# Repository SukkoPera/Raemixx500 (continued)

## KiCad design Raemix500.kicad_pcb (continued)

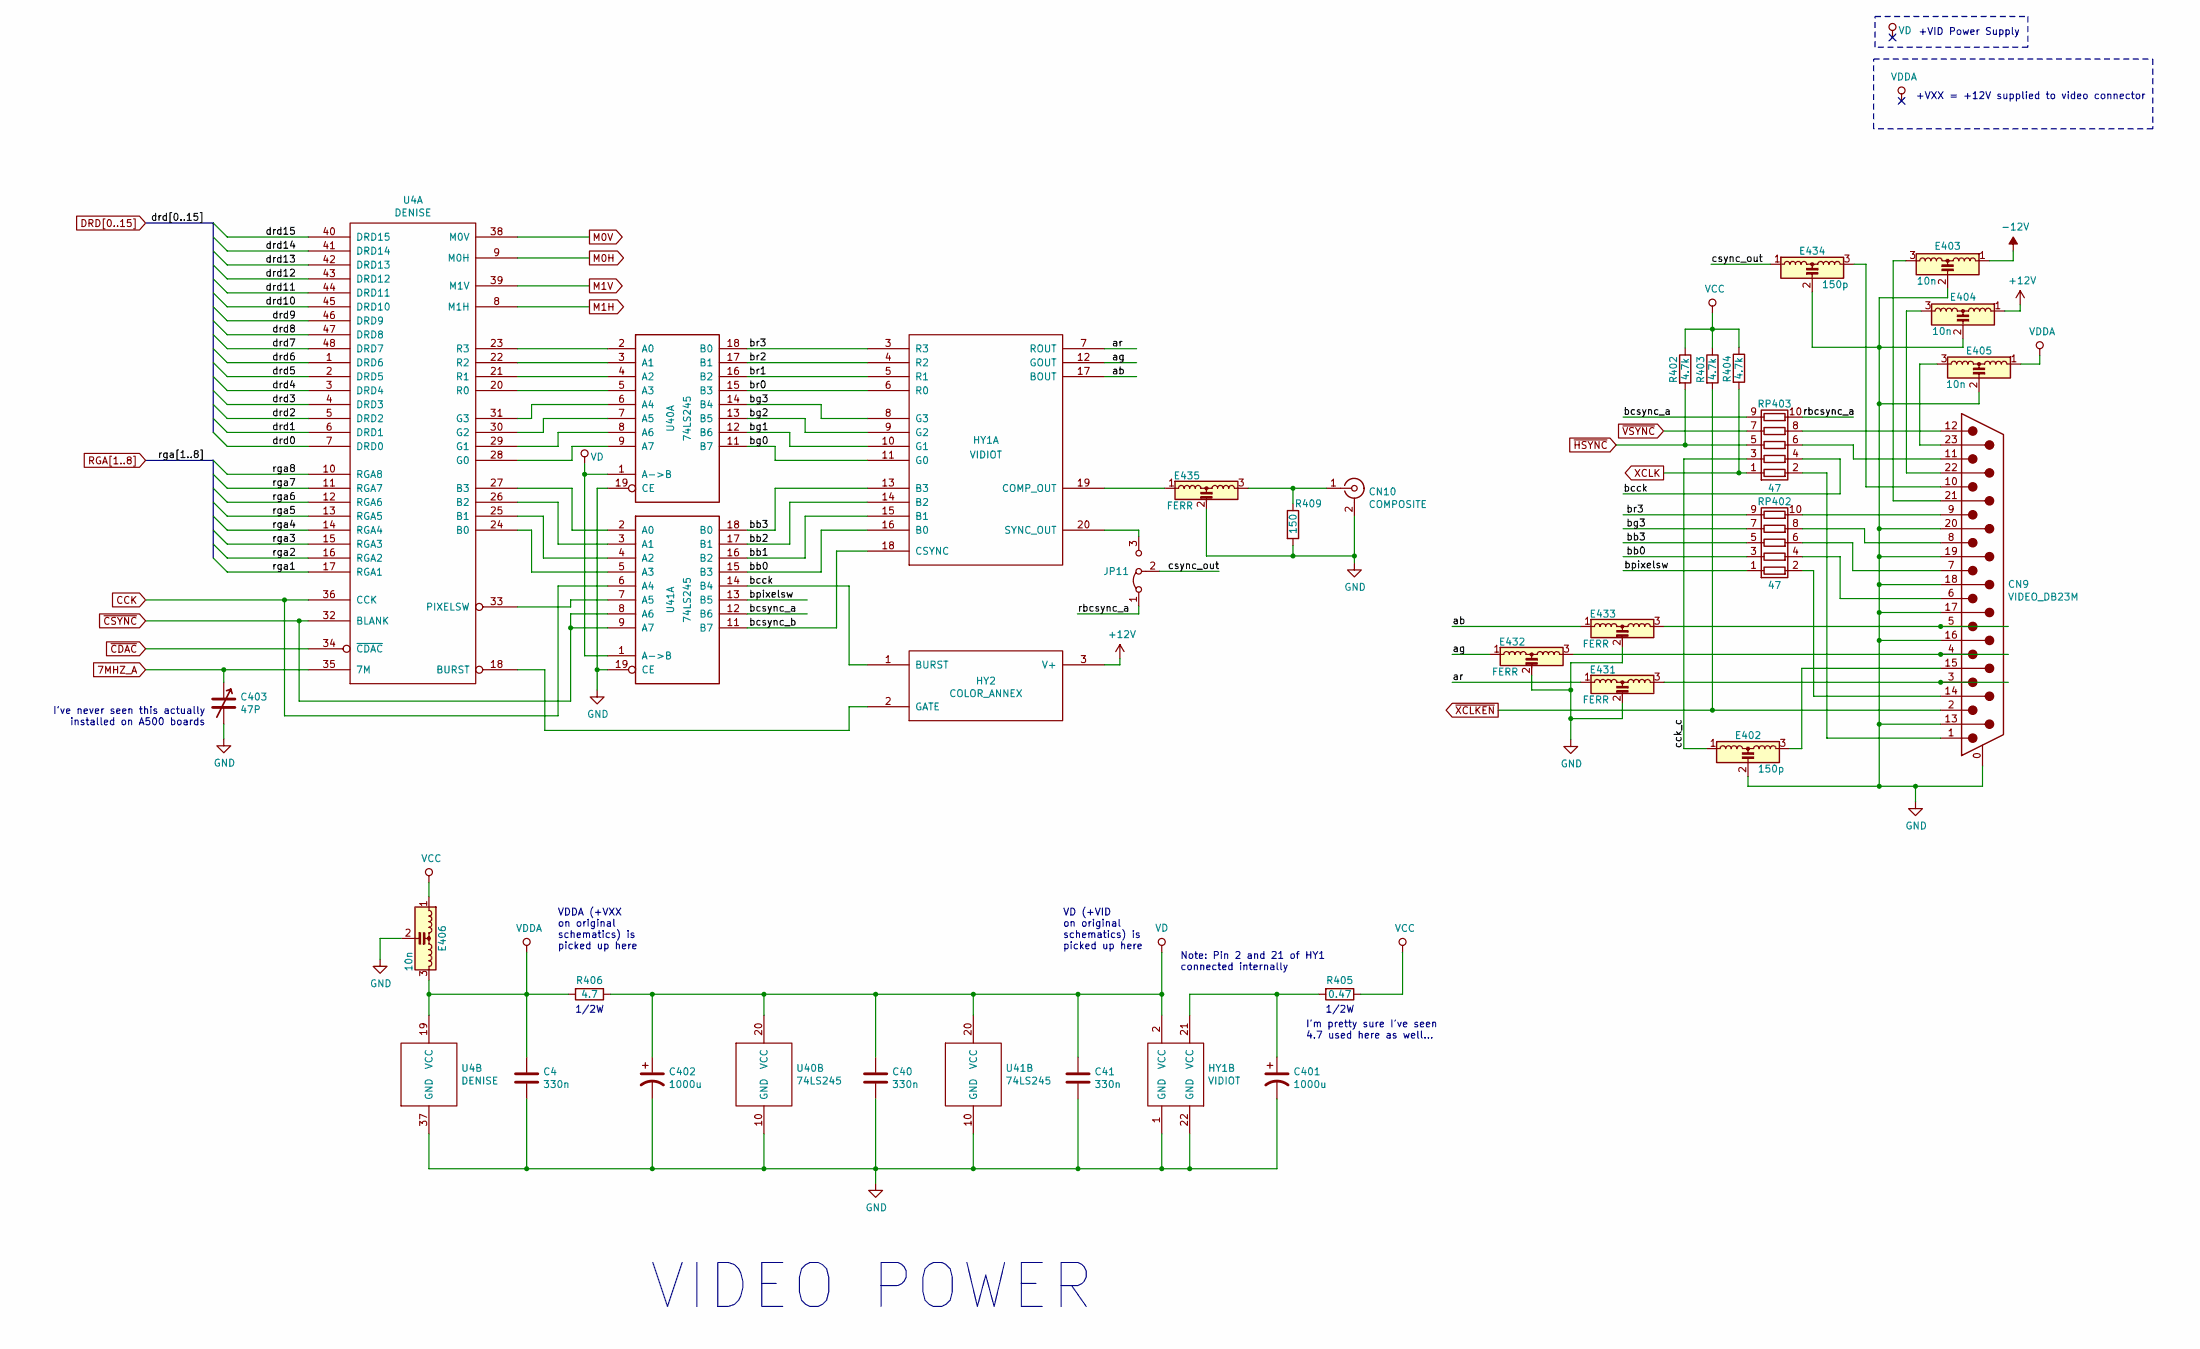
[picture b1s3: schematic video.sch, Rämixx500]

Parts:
C4, C40, C41: 330n; C_Axial_L6.3mm_D2.5mm_P10.16mm
C401, C402: 1000u; CP_Radial_D8.0mm_P5.00mm
C403: 47P; VariCap
CN9: VIDEO_DB23M; DB_23
CN10: COMPOSITE; rca_yellow
E402, E434: 150p; EMI_Filter_Long
E403, E404, E405: 10n; EMI_Filter_Long
E406: 10n; EMI_Filter_Short
E431, E432, E433, E435: FERR; EMI_Filter_Long
HY1: VIDIOT; PinHeader_1x22_P2.54mm_Vertical
HY2: COLOR_ANNEX; PinHeader_1x03_P2.54mm_Vertical
JP11: Jumper_3_Bridged12; Jumper3-Bridged12
R402, R403, R404: 4.7k; R_Axial_DIN0309_L9.0mm_D3.2mm_P12.70mm_Horizontal
R405: 0.47; R_Axial_DIN0309_L9.0mm_D3.2mm_P15.24mm_Horizontal
R406: 4.7; R_Axial_DIN0309_L9.0mm_D3.2mm_P15.24mm_Horizontal
R409: 150; C_Axial_L9.0mm_D3.2mm_P12.70mm
RP402, RP403: 47; R_Array_SIP10
U4: DENISE; DIP-48_W15.24mm_Socket_LongPads
U40, U41: 74LS245; DIP-20_W7.62mm_Socket_LongPads

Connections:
7MHZ_A: C403.1, U4.35 (7M); also elsewhere on the board
+12V: E404.1, HY2.3 (V+); also elsewhere on the board
-12V: E403.1; also elsewhere on the board
/Denise & Video Stuff/ab: E433.1, HY1.17 (BOUT)
/Denise & Video Stuff/ag: E432.1, HY1.12 (GOUT)
/Denise & Video Stuff/ar: E431.1, HY1.7 (ROUT)
/Denise & Video Stuff/bb0: HY1.16 (B0), RP402.3 (R2.1), U41.15 (B3)
/Denise & Video Stuff/bb1: HY1.15 (B1), U41.16 (B2)
/Denise & Video Stuff/bb2: HY1.14 (B2), U41.17 (B1)
/Denise & Video Stuff/bb3: HY1.13 (B3), RP402.5 (R3.1), U41.18 (B0)
/Denise & Video Stuff/bcck: HY2.1 (BURST), RP403.4 (R2.2), U41.14 (B4)
/Denise & Video Stuff/bcsync_a: RP403.9 (R5.1), U41.12 (B6)
/Denise & Video Stuff/bcsync_b: HY1.18 (CSYNC), U41.11 (B7)
/Denise & Video Stuff/bg0: HY1.11 (G0), U40.11 (B7)
/Denise & Video Stuff/bg1: HY1.10 (G1), U40.12 (B6)
/Denise & Video Stuff/bg2: HY1.9 (G2), U40.13 (B5)
/Denise & Video Stuff/bg3: HY1.8 (G3), RP402.7 (R4.1), U40.14 (B4)
/Denise & Video Stuff/bpixelsw: RP402.1 (R1.1), U41.13 (B5)
/Denise & Video Stuff/br0: HY1.6 (R0), U40.15 (B3)
/Denise & Video Stuff/br1: HY1.5 (R1), U40.16 (B2)
/Denise & Video Stuff/br2: HY1.4 (R2), U40.17 (B1)
/Denise & Video Stuff/br3: HY1.3 (R3), RP402.9 (R5.1), U40.18 (B0)
/Denise & Video Stuff/cck_c: E402.1, RP403.3 (R2.1)
/Denise & Video Stuff/csync_out: E434.1, JP11.2 (C)
/Denise & Video Stuff/rbcsync_a: JP11.1 (A), RP403.10 (R5.2)
CCK: U4.36 (CCK), U41.6 (A4); also elsewhere on the board
DRD0: U4.7 (DRD0); also elsewhere on the board
DRD1: U4.6 (DRD1); also elsewhere on the board
DRD2: U4.5 (DRD2); also elsewhere on the board
DRD3: U4.4 (DRD3); also elsewhere on the board
DRD4: U4.3 (DRD4); also elsewhere on the board
DRD5: U4.2 (DRD5); also elsewhere on the board
DRD6: U4.1 (DRD6); also elsewhere on the board
DRD7: U4.48 (DRD7); also elsewhere on the board
DRD8: U4.47 (DRD8); also elsewhere on the board
DRD9: U4.46 (DRD9); also elsewhere on the board
DRD10: U4.45 (DRD10); also elsewhere on the board
DRD11: U4.44 (DRD11); also elsewhere on the board
DRD12: U4.43 (DRD12); also elsewhere on the board
DRD13: U4.42 (DRD13); also elsewhere on the board
DRD14: U4.41 (DRD14); also elsewhere on the board
DRD15: U4.40 (DRD15); also elsewhere on the board
GND: C4.2, C40.2, C41.2, C401.2, C402.2, C403.2, CN9.0 (PAD), CN9.13, CN9.16, CN9.17, CN9.18, CN9.19, CN9.20, CN10.2 (Ext), E402.2, E403.2, E404.2, E405.2, E406.2, E431.2, E432.2, E433.2, E434.2, E435.2, HY1.1 (GND), HY1.22 (GND), R409.2, U4.37 (GND), U40.10 (GND), U40.19 (CE), U41.10 (GND), U41.19 (CE); also elsewhere on the board
M0H: U4.9 (M0H); also elsewhere on the board
M0V: U4.38 (M0V); also elsewhere on the board
M1H: U4.8 (M1H); also elsewhere on the board
M1V: U4.39 (M1V); also elsewhere on the board
unnamed: C401.1, HY1.21 (VCC), R405.2
unnamed: CN9.1, RP403.2 (R1.2)
unnamed: CN9.3, E431.3
unnamed: CN9.4, E432.3
unnamed: CN9.5, E433.3
unnamed: CN9.6, RP402.4 (R2.2)
unnamed: CN9.7, RP402.6 (R3.2)
unnamed: CN9.8, RP402.8 (R4.2)
unnamed: CN9.9, RP402.10 (R5.2)
unnamed: CN9.10, E434.3
unnamed: CN9.11, RP403.6 (R3.2)
unnamed: CN9.12, RP403.8 (R4.2)
unnamed: CN9.14, RP402.2 (R1.2)
unnamed: CN9.15, E402.3
unnamed: CN9.21, E403.3
unnamed: CN9.22, E404.3
unnamed: CN9.23, E405.3
unnamed: CN10.1 (In), E435.3, R409.1
unnamed: E435.1, HY1.19 (COMP_OUT)
unnamed: HY1.20 (SYNC_OUT), JP11.3 (B)
unnamed: HY2.2 (GATE), U4.18 (BURST)
unnamed: U4.20 (R0), U40.5 (A3)
unnamed: U4.21 (R1), U40.4 (A2)
unnamed: U4.22 (R2), U40.3 (A1)
unnamed: U4.23 (R3), U40.2 (A0)
unnamed: U4.24 (B0), U41.5 (A3)
unnamed: U4.25 (B1), U41.4 (A2)
unnamed: U4.26 (B2), U41.3 (A1)
unnamed: U4.27 (B3), U41.2 (A0)
unnamed: U4.28 (G0), U40.9 (A7)
unnamed: U4.29 (G1), U40.8 (A6)
unnamed: U4.30 (G2), U40.7 (A5)
unnamed: U4.31 (G3), U40.6 (A4)
unnamed: U4.33 (PIXELSW), U41.7 (A5)
RGA1: U4.17 (RGA1); also elsewhere on the board
RGA2: U4.16 (RGA2); also elsewhere on the board
RGA3: U4.15 (RGA3); also elsewhere on the board
RGA4: U4.14 (RGA4); also elsewhere on the board
RGA5: U4.13 (RGA5); also elsewhere on the board
RGA6: U4.12 (RGA6); also elsewhere on the board
RGA7: U4.11 (RGA7); also elsewhere on the board
RGA8: U4.10 (RGA8); also elsewhere on the board
VCC: E406.1, R402.1, R403.1, R404.1, R405.1; also elsewhere on the board
VD: C40.1, C41.1, C402.1, HY1.2 (VCC), R406.1, U40.1 (A->B), U40.20 (VCC), U41.1 (A->B), U41.20 (VCC)
VDDA: C4.1, E405.1, E406.3, R406.2, U4.19 (VCC)
XCLK: R404.2, RP403.1 (R1.1); also elsewhere on the board
~CDAC: U4.34 (~CDAC); also elsewhere on the board
~CSYNC: U4.32 (BLANK), U41.8 (A6), U41.9 (A7); also elsewhere on the board
~HSYNC: R402.2, RP403.5 (R3.1); also elsewhere on the board
~VSYNC: RP403.7 (R4.1); also elsewhere on the board

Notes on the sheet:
I've never seen this actually installed on A500 boards
+VID Power Supply
+VXX = +12V supplied to video connector
VDDA (+VXX on original schematics) is picked up here
1/2W
VD (+VID on original schematics) is picked up here
I'm pretty sure I've seen 4.7 used here as well...
Note: Pin 2 and 21 of HY1 connected internally
VIDEO POWER

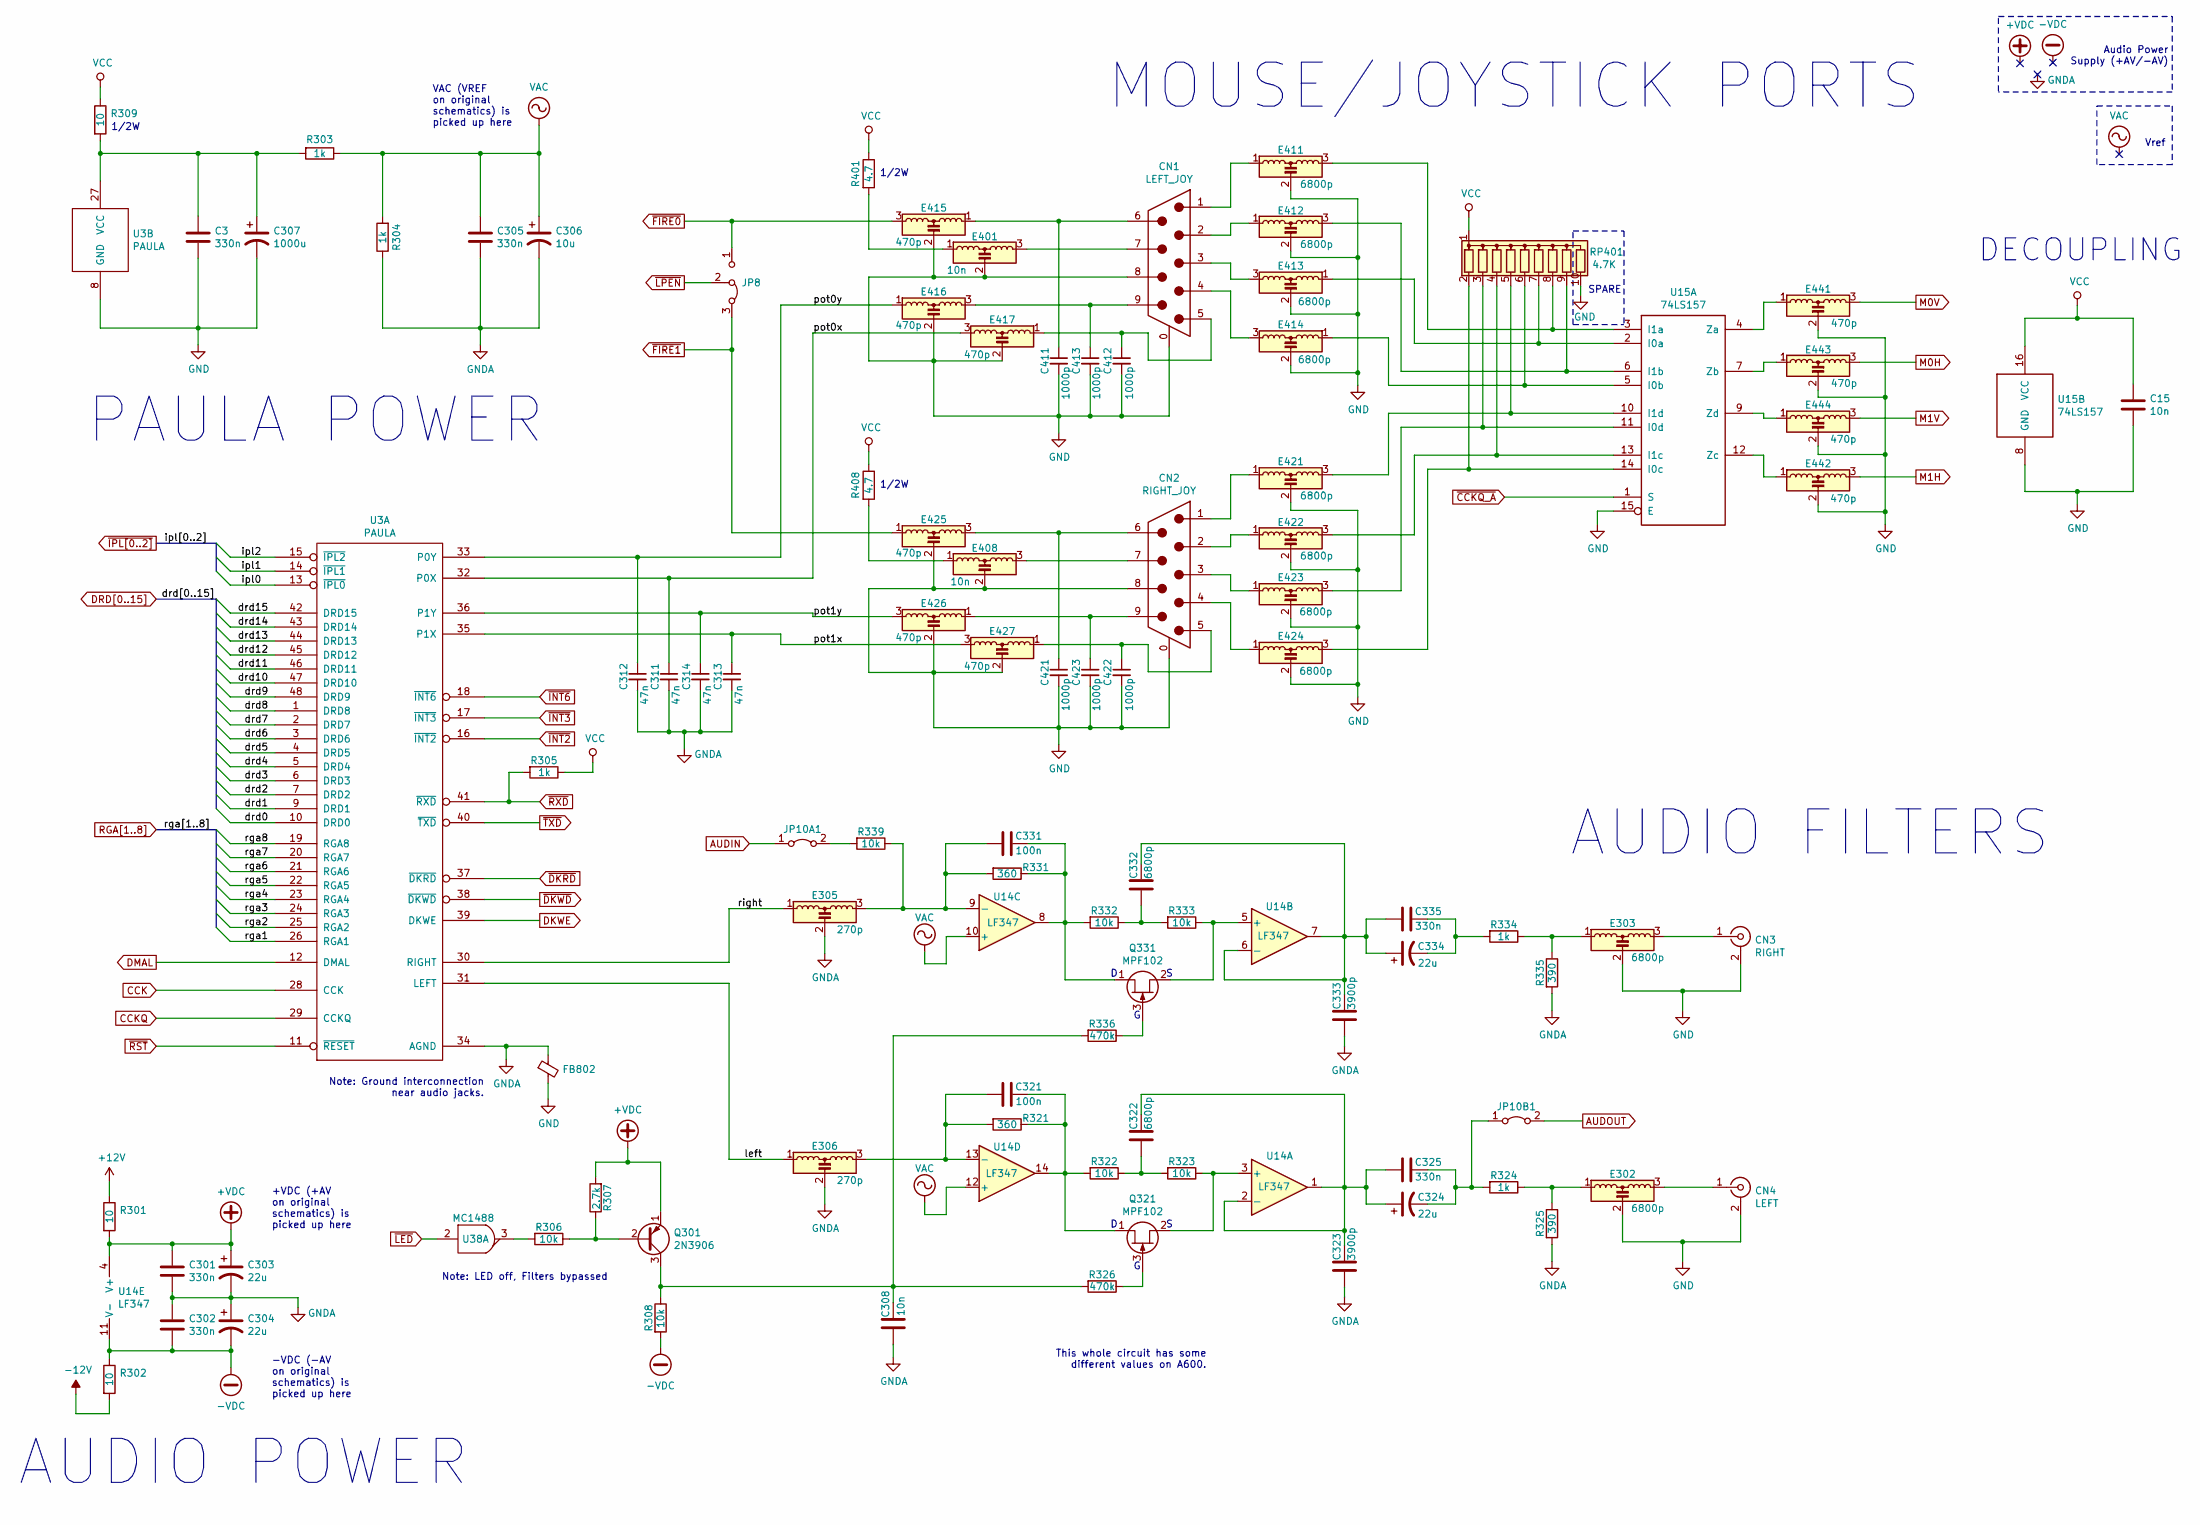
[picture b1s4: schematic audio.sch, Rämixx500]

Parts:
C3: 330n; C_Axial_L6.3mm_D2.5mm_P10.16mm
C15: 10n; C_Axial_L6.3mm_D2.5mm_P10.16mm
C301, C302, C305, C325, C335: 330n; C_Axial_L9.0mm_D3.2mm_P12.70mm
C303, C304: 22u; CP_Radial_D5.0mm_P2.00mm
C306: 10u; CP_Radial_D8.0mm_P5.00mm
C307: 1000u; CP_Radial_D8.0mm_P5.00mm
C308: 10n; C_Axial_L9.0mm_D3.2mm_P12.70mm
C311, C312, C313, C314: 47n; C_Axial_L9.0mm_D3.2mm_P12.70mm
C321, C331: 100n; C_Axial_L9.0mm_D3.2mm_P12.70mm
C322, C332: 6800p; C_Axial_L9.0mm_D3.2mm_P12.70mm
C323, C333: 3900p; C_Axial_L9.0mm_D3.2mm_P12.70mm
C324, C334: 22u; CP_Radial_D8.0mm_P5.00mm
C411, C412, C413, C421, C422, C423: 1000p; C_Axial_L9.0mm_D3.2mm_P12.70mm
CN1: LEFT_JOY; DB_9M
CN2: RIGHT_JOY; DB_9M
CN3: RIGHT; rca_red
CN4: LEFT; rca_white
E302, E303: 6800p; EMI_Filter_Short
E305, E306: 270p; EMI_Filter_Long
E401, E408: 10n; EMI_Filter_Long
E411, E412, E413, E414, E421, E422, E423, E424: 6800p; EMI_Filter_Long
E415, E416, E417, E425, E426, E427, E441, E442, E443, E444: 470p; EMI_Filter_Long
FB802: Ferrite_Bead_Small; Ferrite_Axial_L9.0mm_D3.2mm_P12.70mm
JP8: Jumper_3_Bridged23; Jumper3-Bridged23
JP10A1, JP10B1: Jumper_2_Bridged; Jumper2-Bridged
Q301: 2N3906; TO-92L_Inline_Wide
Q321, Q331: MPF102; TO-92L_Inline_Wide
R301, R302: 10; R_Axial_DIN0309_L9.0mm_D3.2mm_P12.70mm_Horizontal
R303, R304, R305, R324, R334: 1k; R_Axial_DIN0309_L9.0mm_D3.2mm_P12.70mm_Horizontal
R306, R308, R322, R323, R332, R333, R339: 10k; R_Axial_DIN0309_L9.0mm_D3.2mm_P12.70mm_Horizontal
R307: 2.7k; R_Axial_DIN0309_L9.0mm_D3.2mm_P12.70mm_Horizontal
R309: 10; R_Axial_DIN0309_L9.0mm_D3.2mm_P15.24mm_Horizontal
R321, R331: 360; R_Axial_DIN0309_L9.0mm_D3.2mm_P12.70mm_Horizontal
R325, R335: 390; R_Axial_DIN0309_L9.0mm_D3.2mm_P12.70mm_Horizontal
R326, R336: 470k; R_Axial_DIN0309_L9.0mm_D3.2mm_P12.70mm_Horizontal
R401, R408: 4.7; R_Axial_DIN0309_L9.0mm_D3.2mm_P15.24mm_Horizontal
RP401: 4.7K; R_Array_SIP10
U3: PAULA; DIP-48_W15.24mm_Socket_LongPads
U14: LF347; DIP-14_W7.62mm_Socket_LongPads
U15: 74LS157; DIP-16_W7.62mm_Socket_LongPads
U38: MC1488; DIP-14_W7.62mm_Socket_LongPads

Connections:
+12V: R301.1; also elsewhere on the board
+VDC: C301.1, C303.1, Q301.1 (E), R301.2, R307.2, U14.4 (V+)
-12V: R302.2; also elsewhere on the board
-VDC: C302.2, C304.2, R302.1, R308.2, U14.11 (V-)
/Paula & Audio Stuff/left: E306.1, U3.31 (LEFT)
/Paula & Audio Stuff/pot0x: C311.1, E417.3, U3.32 (P0X)
/Paula & Audio Stuff/pot0y: C312.1, E416.1, U3.33 (P0Y)
/Paula & Audio Stuff/pot1x: C313.1, E427.3, U3.35 (P1X)
/Paula & Audio Stuff/pot1y: C314.1, E426.3, U3.36 (P1Y)
/Paula & Audio Stuff/right: E305.1, U3.30 (RIGHT)
AUDIN: JP10A1.1 (A); also elsewhere on the board
AUDOUT: JP10B1.2 (B); also elsewhere on the board
CCK: U3.28 (CCK); also elsewhere on the board
CCKQ: U3.29 (CCKQ); also elsewhere on the board
DKWE: U3.39 (DKWE); also elsewhere on the board
DMAL: U3.12 (DMAL); also elsewhere on the board
DRD0: U3.10 (DRD0); also elsewhere on the board
DRD1: U3.9 (DRD1); also elsewhere on the board
DRD2: U3.7 (DRD2); also elsewhere on the board
DRD3: U3.6 (DRD3); also elsewhere on the board
DRD4: U3.5 (DRD4); also elsewhere on the board
DRD5: U3.4 (DRD5); also elsewhere on the board
DRD6: U3.3 (DRD6); also elsewhere on the board
DRD7: U3.2 (DRD7); also elsewhere on the board
DRD8: U3.1 (DRD8); also elsewhere on the board
DRD9: U3.48 (DRD9); also elsewhere on the board
DRD10: U3.47 (DRD10); also elsewhere on the board
DRD11: U3.46 (DRD11); also elsewhere on the board
DRD12: U3.45 (DRD12); also elsewhere on the board
DRD13: U3.44 (DRD13); also elsewhere on the board
DRD14: U3.43 (DRD14); also elsewhere on the board
DRD15: U3.42 (DRD15); also elsewhere on the board
GND: C3.2, C15.2, C307.2, C411.2, C412.2, C413.2, C421.2, C422.2, C423.2, CN1.0 (PAD), CN1.8, CN2.0 (PAD), CN2.8, CN3.2 (Ext), CN4.2 (Ext), E302.2, E303.2, E401.2, E408.2, E411.2, E412.2, E413.2, E414.2, E415.2, E416.2, E417.2, E421.2, E422.2, E423.2, E424.2, E425.2, E426.2, E427.2, E441.2, E442.2, E443.2, E444.2, FB802.2, RP401.10 (R9), U3.8 (GND), U15.8 (GND), U15.15 (E); also elsewhere on the board
GNDA: C301.2, C302.1, C303.2, C304.1, C305.2, C306.2, C308.2, C311.2, C312.2, C313.2, C314.2, C323.2, C333.2, E305.2, E306.2, FB802.1, R304.1, R325.2, R335.2, U3.34 (AGND)
M0H: E443.3; also elsewhere on the board
M0V: E441.3; also elsewhere on the board
M1H: E442.3; also elsewhere on the board
M1V: E444.3; also elsewhere on the board
unnamed: C3.1, C307.1, R303.2, R309.2, U3.27 (VCC)
unnamed: C308.1, Q301.3 (C), R308.1, R326.2, R336.2
unnamed: C321.1, Q321.1 (D), R321.1, R322.2, U14.14
unnamed: C321.2, E306.3, R321.2, U14.13 (-)
unnamed: C322.1, C323.1, C324.1, C325.2, U14.1, U14.2 (-)
unnamed: C322.2, R322.1, R323.2
unnamed: C324.2, C325.1, JP10B1.1 (A), R324.2
unnamed: C331.1, Q331.1 (D), R331.1, R332.2, U14.8
unnamed: C331.2, E305.3, R331.2, R339.1, U14.9 (-)
unnamed: C332.1, C333.1, C334.1, C335.2, U14.6 (-), U14.7
unnamed: C332.2, R332.1, R333.2
unnamed: C334.2, C335.1, R334.2
unnamed: C411.1, CN1.6, E415.1
unnamed: C412.1, CN1.5, E417.1
unnamed: C413.1, CN1.9, E416.3
unnamed: C421.1, CN2.6, E425.3
unnamed: C422.1, CN2.5, E427.1
unnamed: C423.1, CN2.9, E426.1
unnamed: CN1.1, E411.1
unnamed: CN1.2, E412.1
unnamed: CN1.3, E413.3
unnamed: CN1.4, E414.3
unnamed: CN1.7, E401.3
unnamed: CN2.1, E421.1
unnamed: CN2.2, E422.1
unnamed: CN2.3, E423.1
unnamed: CN2.4, E424.1
unnamed: CN2.7, E408.3
unnamed: CN3.1 (In), E303.3
unnamed: CN4.1 (In), E302.3
unnamed: E302.1, R324.1, R325.1
unnamed: E303.1, R334.1, R335.1
unnamed: E401.1, R401.2
unnamed: E408.1, R408.2
unnamed: E411.3, RP401.8 (R7), U15.3 (I1a)
unnamed: E412.3, RP401.9 (R8), U15.6 (I1b)
unnamed: E413.1, RP401.7 (R6), U15.2 (I0a)
unnamed: E414.1, RP401.6 (R5), U15.5 (I0b)
unnamed: E421.3, RP401.5 (R4), U15.10 (I1d)
unnamed: E422.3, RP401.4 (R3), U15.13 (I1c)
unnamed: E423.3, RP401.3 (R2), U15.11 (I0d)
unnamed: E424.3, RP401.2 (R1), U15.14 (I0c)
unnamed: E441.1, U15.4 (Za)
unnamed: E442.1, U15.12 (Zc)
unnamed: E443.1, U15.7 (Zb)
unnamed: E444.1, U15.9 (Zd)
unnamed: JP10A1.2 (B), R339.2
unnamed: Q301.2 (B), R306.1, R307.1
unnamed: Q321.2 (S), R323.1, U14.3 (+)
unnamed: Q321.3 (G), R326.1
unnamed: Q331.2 (S), R333.1, U14.5 (+)
unnamed: Q331.3 (G), R336.1
unnamed: R306.2, U38.3
RGA1: U3.26 (RGA1); also elsewhere on the board
RGA2: U3.25 (RGA2); also elsewhere on the board
RGA3: U3.24 (RGA3); also elsewhere on the board
RGA4: U3.23 (RGA4); also elsewhere on the board
RGA5: U3.22 (RGA5); also elsewhere on the board
RGA6: U3.21 (RGA6); also elsewhere on the board
RGA7: U3.20 (RGA7); also elsewhere on the board
RGA8: U3.19 (RGA8); also elsewhere on the board
VAC: C305.1, C306.1, R303.1, R304.2, U14.10 (+), U14.12 (+)
VCC: C15.1, R305.1, R309.1, R401.1, R408.1, RP401.1 (common), U15.16 (VCC); also elsewhere on the board
~CCKQ_A: U15.1 (S); also elsewhere on the board
~DKRD: U3.37 (~DKRD); also elsewhere on the board
~DKWD: U3.38 (~DKWD); also elsewhere on the board
~FIRE0: E415.3, JP8.1 (A); also elsewhere on the board
~FIRE1: E425.1, JP8.3 (B); also elsewhere on the board
~INT2: U3.16 (~INT2); also elsewhere on the board
~INT3: U3.17 (~INT3); also elsewhere on the board
~INT6: U3.18 (~INT6); also elsewhere on the board
~IPL0: U3.13 (~IPL0); also elsewhere on the board
~IPL1: U3.14 (~IPL1); also elsewhere on the board
~IPL2: U3.15 (~IPL2); also elsewhere on the board
~LED: U38.2; also elsewhere on the board
~LPEN: JP8.2 (C); also elsewhere on the board
~RST: U3.11 (~RESET); also elsewhere on the board
~RXD: R305.2, U3.41 (~RXD); also elsewhere on the board
~TXD: U3.40 (~TXD); also elsewhere on the board

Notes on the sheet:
Note: Ground interconnection near audio jacks.
Audio Power Supply (+AV/-AV)
1/2W
SPARE
Vref
Note: LED off, Filters bypassed
AUDIO FILTERS
MOUSE/JOYSTICK PORTS
This whole circuit has some different values on A600.
VAC (VREF on original schematics) is picked up here
+VDC (+AV on original schematics) is picked up here
-VDC (-AV on original schematics) is picked up here
PAULA POWER
AUDIO POWER
DECOUPLING

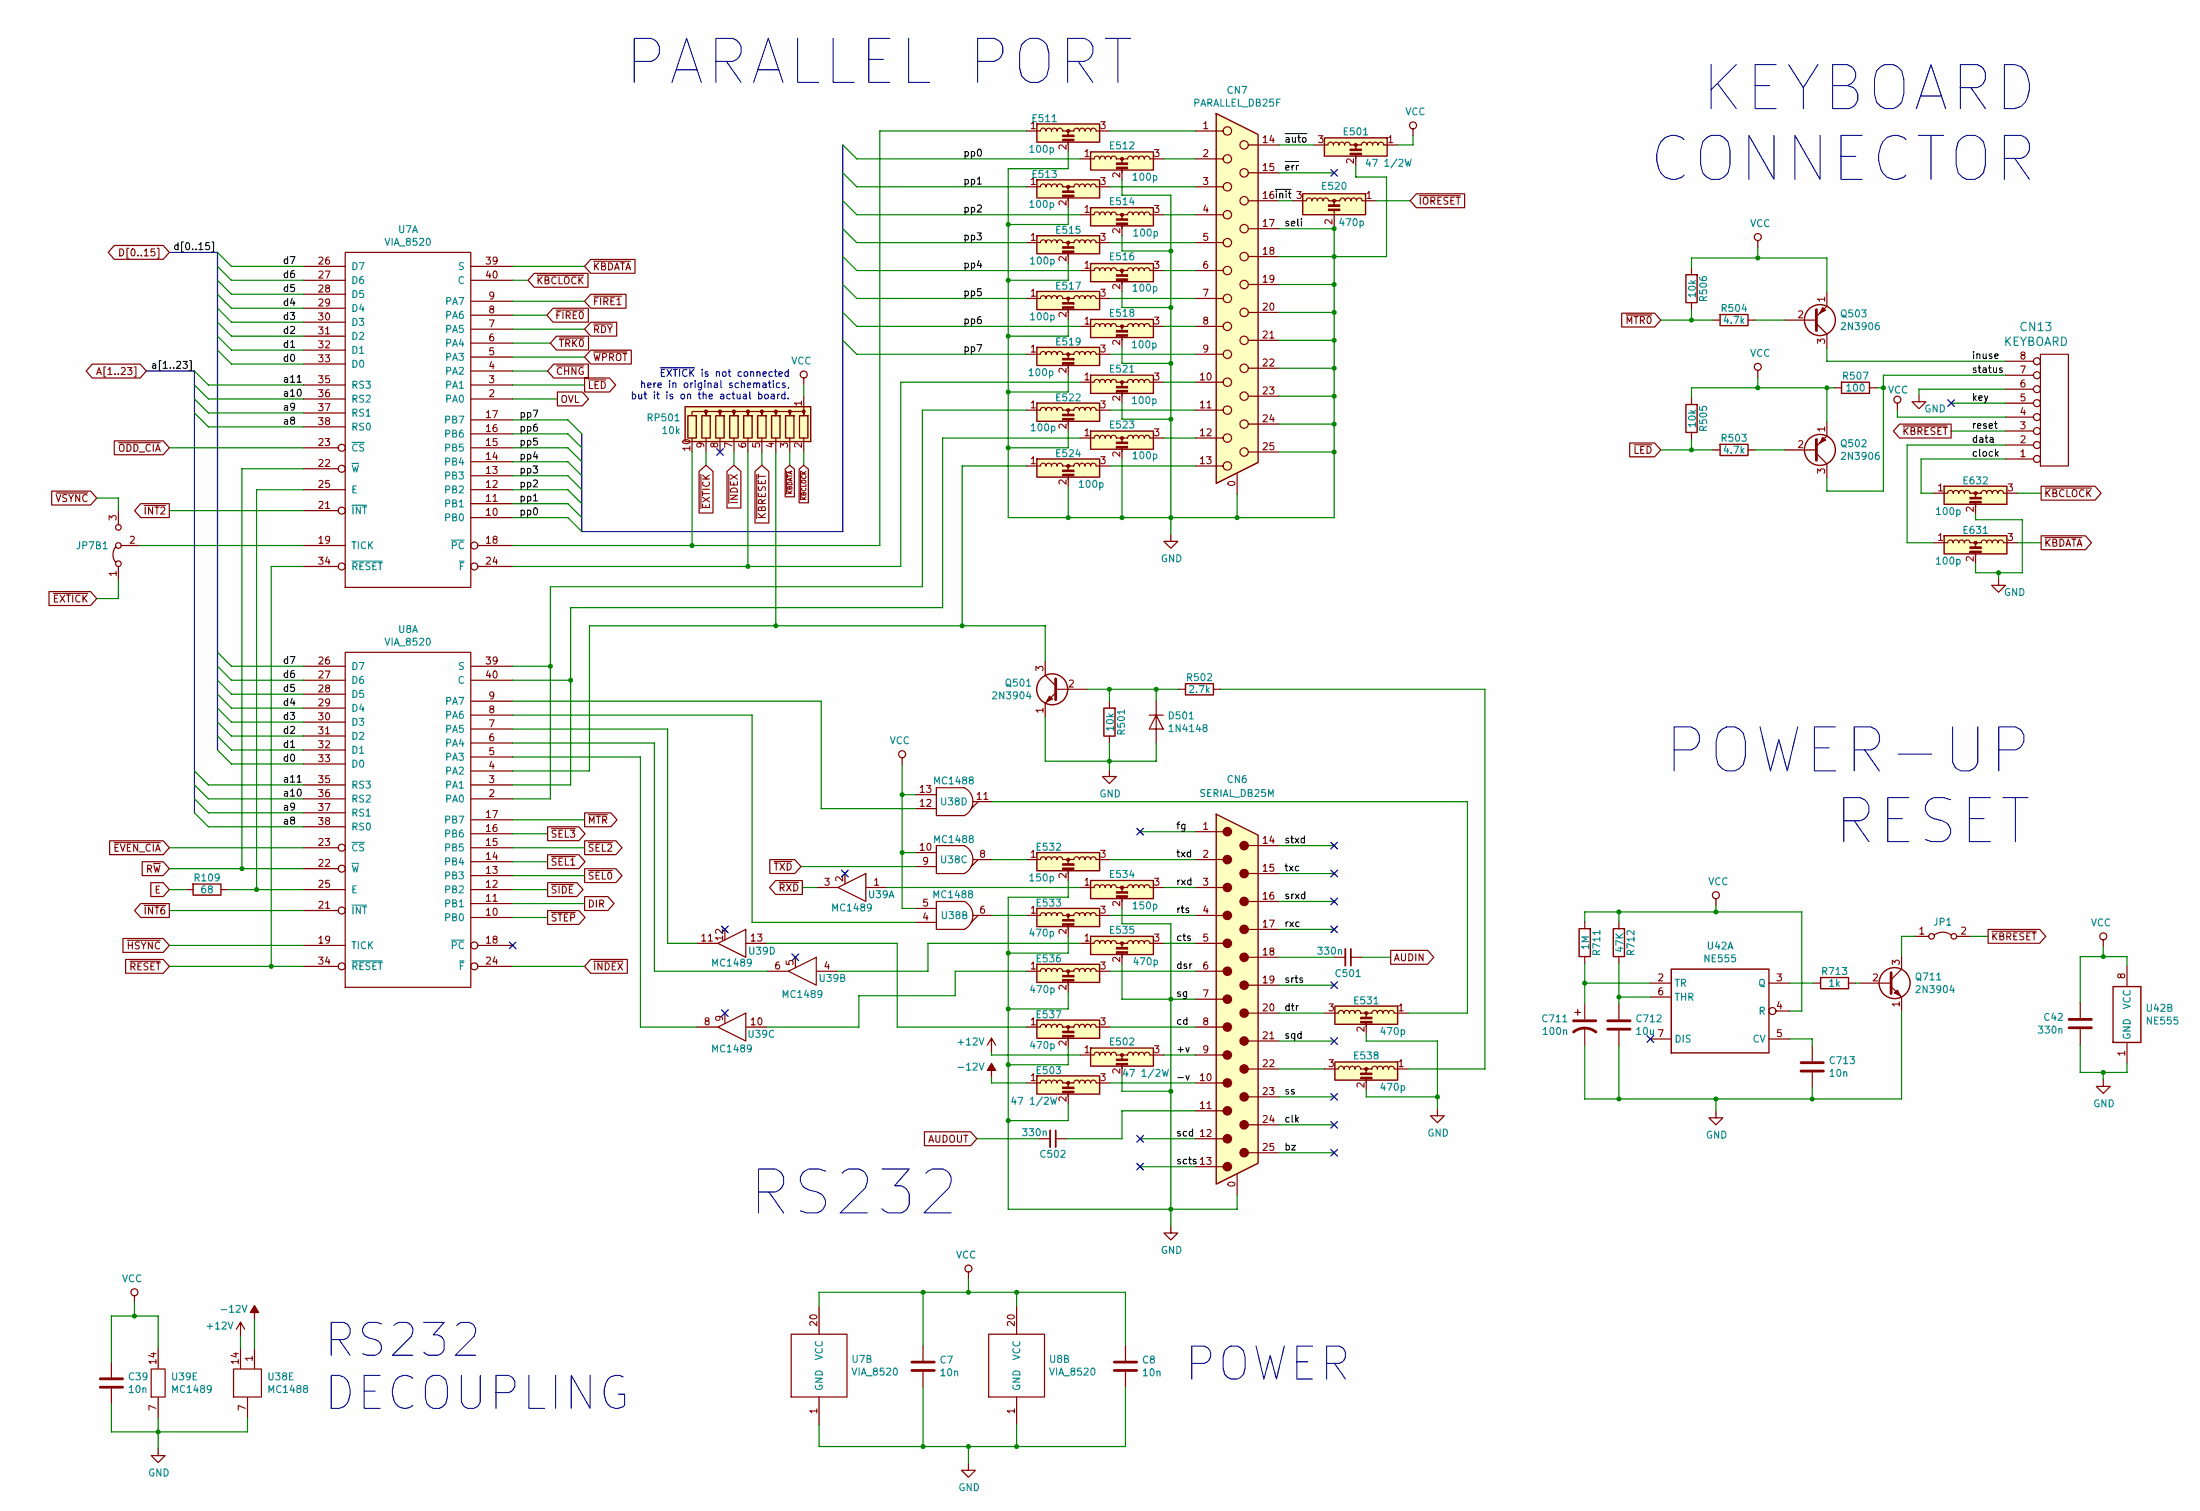
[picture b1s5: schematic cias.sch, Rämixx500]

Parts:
C7, C8: 10n; C_Axial_L6.3mm_D2.5mm_P10.16mm
C39, C713: 10n; C_Axial_L9.0mm_D3.2mm_P12.70mm
C42: 330n; C_Axial_L6.3mm_D2.5mm_P10.16mm
C501, C502: 330n; C_Axial_L9.0mm_D3.2mm_P12.70mm
C711: 100n; C_Axial_L9.0mm_D3.2mm_P12.70mm
C712: 10u; CP_Radial_D8.0mm_P5.00mm
CN6: SERIAL_DB25M; DB_25M
CN7: PARALLEL_DB25F; DB_25M
CN13: KEYBOARD; PinHeader_1x08_P2.54mm_Vertical
D501: 1N4148; D_DO-35_SOD27_P12.70mm_Horizontal
E501, E502, E503: 47 1/2W; EMI_Filter_Longer
E511, E512, E513, E514, E515, E516, E517, E518, E519, E521, E522, E523, E524, E631, E632: 100p; EMI_Filter_Short
E520, E531, E533, E535, E536, E537, E538: 470p; EMI_Filter_Short
E532, E534: 150p; EMI_Filter_Short
JP1: Jumper_2_Bridged; Jumper2-Bridged
JP7B1: Jumper_3_Bridged12; Jumper3-Bridged12
Q501, Q711: 2N3904; TO-92L_Inline_Wide
Q502, Q503: 2N3906; TO-92L_Inline_Wide
R109: 68; R_Axial_DIN0309_L9.0mm_D3.2mm_P12.70mm_Horizontal
R501, R505, R506: 10k; R_Axial_DIN0309_L9.0mm_D3.2mm_P12.70mm_Horizontal
R502: 2.7k; R_Axial_DIN0309_L9.0mm_D3.2mm_P12.70mm_Horizontal
R503, R504: 4.7k; R_Axial_DIN0309_L9.0mm_D3.2mm_P12.70mm_Horizontal
R507: 100; R_Axial_DIN0309_L9.0mm_D3.2mm_P12.70mm_Horizontal
R711: 1M; R_Axial_DIN0309_L9.0mm_D3.2mm_P12.70mm_Horizontal
R712: 47K; R_Axial_DIN0309_L9.0mm_D3.2mm_P12.70mm_Horizontal
R713: 1k; R_Axial_DIN0309_L9.0mm_D3.2mm_P12.70mm_Horizontal
RP501: 10k; R_Array_SIP10
U7, U8: VIA_8520; DIP-40_W15.24mm_Socket_LongPads
U38: MC1488; DIP-14_W7.62mm_Socket_LongPads
U39: MC1489; DIP-14_W7.62mm_Socket_LongPads
U42: NE555; DIP-8_W7.62mm_Socket_LongPads

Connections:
+12V: E502.1, U38.14 (VCC); also elsewhere on the board
-12V: E503.1, U38.1 (VEE); also elsewhere on the board
/Parallel & Serial/+v: CN6.9, E502.3
/Parallel & Serial/-v: CN6.10, E503.3
/Parallel & Serial/cd: CN6.8, E537.3
/Parallel & Serial/clock: CN13.1, E632.1
/Parallel & Serial/cts: CN6.5, E535.3
/Parallel & Serial/data: CN13.2, E631.1
/Parallel & Serial/dsr: CN6.6, E536.3
/Parallel & Serial/dtr: CN6.20, E531.3
/Parallel & Serial/inuse: CN13.8, Q503.3 (C)
/Parallel & Serial/pp0: E512.1, U7.10 (PB0)
/Parallel & Serial/pp1: E513.1, U7.11 (PB1)
/Parallel & Serial/pp2: E514.1, U7.12 (PB2)
/Parallel & Serial/pp3: E515.1, U7.13 (PB3)
/Parallel & Serial/pp4: E516.1, U7.14 (PB4)
/Parallel & Serial/pp5: E517.1, U7.15 (PB5)
/Parallel & Serial/pp6: E518.1, U7.16 (PB6)
/Parallel & Serial/pp7: E519.1, U7.17 (PB7)
/Parallel & Serial/rts: CN6.4, E533.3
/Parallel & Serial/rxd: CN6.3, E534.3
/Parallel & Serial/status: CN13.7, Q502.3 (C), R507.1
/Parallel & Serial/txd: CN6.2, E532.3
/Parallel & Serial/~auto: CN7.14, E501.3
/Parallel & Serial/~init: CN7.16, E520.3
A8: U7.38 (RS0), U8.38 (RS0); also elsewhere on the board
A9: U7.37 (RS1), U8.37 (RS1); also elsewhere on the board
A10: U7.36 (RS2), U8.36 (RS2); also elsewhere on the board
A11: U7.35 (RS3), U8.35 (RS3); also elsewhere on the board
AUDIN: C501.1; also elsewhere on the board
AUDOUT: C502.2; also elsewhere on the board
D0: U7.33 (D0), U8.33 (D0); also elsewhere on the board
D1: U7.32 (D1), U8.32 (D1); also elsewhere on the board
D2: U7.31 (D2), U8.31 (D2); also elsewhere on the board
D3: U7.30 (D3), U8.30 (D3); also elsewhere on the board
D4: U7.29 (D4), U8.29 (D4); also elsewhere on the board
D5: U7.28 (D5), U8.28 (D5); also elsewhere on the board
D6: U7.27 (D6), U8.27 (D6); also elsewhere on the board
D7: U7.26 (D7), U8.26 (D7); also elsewhere on the board
DIR: U8.11 (PB1); also elsewhere on the board
E: R109.2; also elsewhere on the board
GND: C7.2, C8.2, C39.2, C42.2, C711.2, C712.2, C713.2, CN6.0 (PAD), CN6.7, CN7.0 (PAD), CN7.17, CN7.18, CN7.19, CN7.20, CN7.21, CN7.22, CN7.23, CN7.24, CN7.25, CN13.6, D501.2 (A), E501.2, E502.2, E503.2, E511.2, E512.2, E513.2, E514.2, E515.2, E516.2, E517.2, E518.2, E519.2, E520.2, E521.2, E522.2, E523.2, E524.2, E531.2, E532.2, E533.2, E534.2, E535.2, E536.2, E537.2, E538.2, E631.2, E632.2, Q501.1 (E), Q711.1 (E), R501.1, U7.1 (GND), U8.1 (GND), U38.7 (GND), U39.7 (GND), U42.1 (GND); also elsewhere on the board
unnamed: C501.2, CN6.18
unnamed: C502.1, CN6.11
unnamed: C711.1, R711.1, U42.2 (TR)
unnamed: C712.1, R712.1, U42.6 (THR)
unnamed: C713.1, U42.5 (CV)
unnamed: CN6.22, E538.3
unnamed: CN7.1, E511.3
unnamed: CN7.2, E512.3
unnamed: CN7.3, E513.3
unnamed: CN7.4, E514.3
unnamed: CN7.5, E515.3
unnamed: CN7.6, E516.3
unnamed: CN7.7, E517.3
unnamed: CN7.8, E518.3
unnamed: CN7.9, E519.3
unnamed: CN7.10, E521.3
unnamed: CN7.11, E522.3
unnamed: CN7.12, E523.3
unnamed: CN7.13, E524.3
unnamed: D501.1 (K), Q501.2 (B), R501.2, R502.2
unnamed: E511.1, RP501.10 (R9), U7.18 (~PC)
unnamed: E521.1, RP501.6 (R5), U7.24 (~F)
unnamed: E522.1, U8.2 (PA0), U8.39 (S)
unnamed: E523.1, U8.3 (PA1), U8.40 (C)
unnamed: E524.1, Q501.3 (C), RP501.4 (R3), U8.4 (PA2)
unnamed: E531.1, U38.11 (OUT_D)
unnamed: E532.1, U38.8 (OUT_C)
unnamed: E533.1, U38.6 (OUT_B)
unnamed: E534.1, U39.1 (IN_A)
unnamed: E535.1, U39.4 (IN_B)
unnamed: E536.1, U39.10 (IN_C)
unnamed: E537.1, U39.13 (IN_D)
unnamed: E538.1, R502.1
unnamed: JP1.1 (A), Q711.3 (C)
unnamed: JP7B1.2 (C), U7.19 (TICK)
unnamed: Q502.2 (B), R503.1
unnamed: Q503.2 (B), R504.1
unnamed: Q711.2 (B), R713.1
unnamed: R109.1, U7.25 (E), U8.25 (E)
unnamed: R713.2, U42.3 (Q)
unnamed: U8.8 (PA6), U38.4 (IN1_B)
unnamed: U8.9 (PA7), U38.12 (IN2_D)
unnamed: U8.6 (PA4), U39.6 (OUT_B)
unnamed: U8.5 (PA3), U39.8 (OUT_C)
unnamed: U8.7 (PA5), U39.11 (OUT_D)
OVL: U7.2 (PA0); also elsewhere on the board
R~W: U7.22 (~W), U8.22 (~W); also elsewhere on the board
VCC: C7.1, C8.1, C39.1, C42.1, CN13.4, E501.1, Q502.1 (E), Q503.1 (E), R505.2, R506.2, R507.2, R711.2, R712.2, RP501.1 (common), U7.20 (VCC), U8.20 (VCC), U38.5 (IN2_B), U38.10 (IN1_C), U38.13 (IN1_D), U39.14 (VCC), U42.4 (R), U42.8 (VCC); also elsewhere on the board
~CHNG: U7.4 (PA2); also elsewhere on the board
~EVEN_CIA: U8.23 (~CS); also elsewhere on the board
~EXTICK: JP7B1.1 (A), RP501.9 (R8); also elsewhere on the board
~FIRE0: U7.8 (PA6); also elsewhere on the board
~FIRE1: U7.9 (PA7); also elsewhere on the board
~HSYNC: U8.19 (TICK); also elsewhere on the board
~INDEX: RP501.7 (R6), U8.24 (~F); also elsewhere on the board
~INT2: U7.21 (~INT); also elsewhere on the board
~INT6: U8.21 (~INT); also elsewhere on the board
~IORESET: E520.1; also elsewhere on the board
~KBCLOCK: E632.3, RP501.2 (R1), U7.40 (C)
~KBDATA: E631.3, RP501.3 (R2), U7.39 (S)
~KBRESET: CN13.3, JP1.2 (B), RP501.5 (R4); also elsewhere on the board
~LED: R503.2, R505.1, U7.3 (PA1); also elsewhere on the board
~MTR: U8.17 (PB7); also elsewhere on the board
~MTR0: R504.2, R506.1; also elsewhere on the board
~ODD_CIA: U7.23 (~CS); also elsewhere on the board
~RDY: U7.7 (PA5); also elsewhere on the board
~RESET: U7.34 (~RESET), U8.34 (~RESET); also elsewhere on the board
~RXD: U39.3 (OUT_A); also elsewhere on the board
~SEL0: U8.13 (PB3); also elsewhere on the board
~SEL1: U8.14 (PB4); also elsewhere on the board
~SEL2: U8.15 (PB5); also elsewhere on the board
~SEL3: U8.16 (PB6); also elsewhere on the board
~SIDE: U8.12 (PB2); also elsewhere on the board
~STEP: U8.10 (PB0); also elsewhere on the board
~TRK0: U7.6 (PA4); also elsewhere on the board
~TXD: U38.9 (IN2_C); also elsewhere on the board
~VSYNC: JP7B1.3 (B); also elsewhere on the board
~WPROT: U7.5 (PA3); also elsewhere on the board

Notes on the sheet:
~EXTICK~ is not connected here in original schematics, but it is on the actual board.
RS232
PARALLEL PORT
RS232 DECOUPLING
KEYBOARD CONNECTOR
POWER-UP RESET
POWER
